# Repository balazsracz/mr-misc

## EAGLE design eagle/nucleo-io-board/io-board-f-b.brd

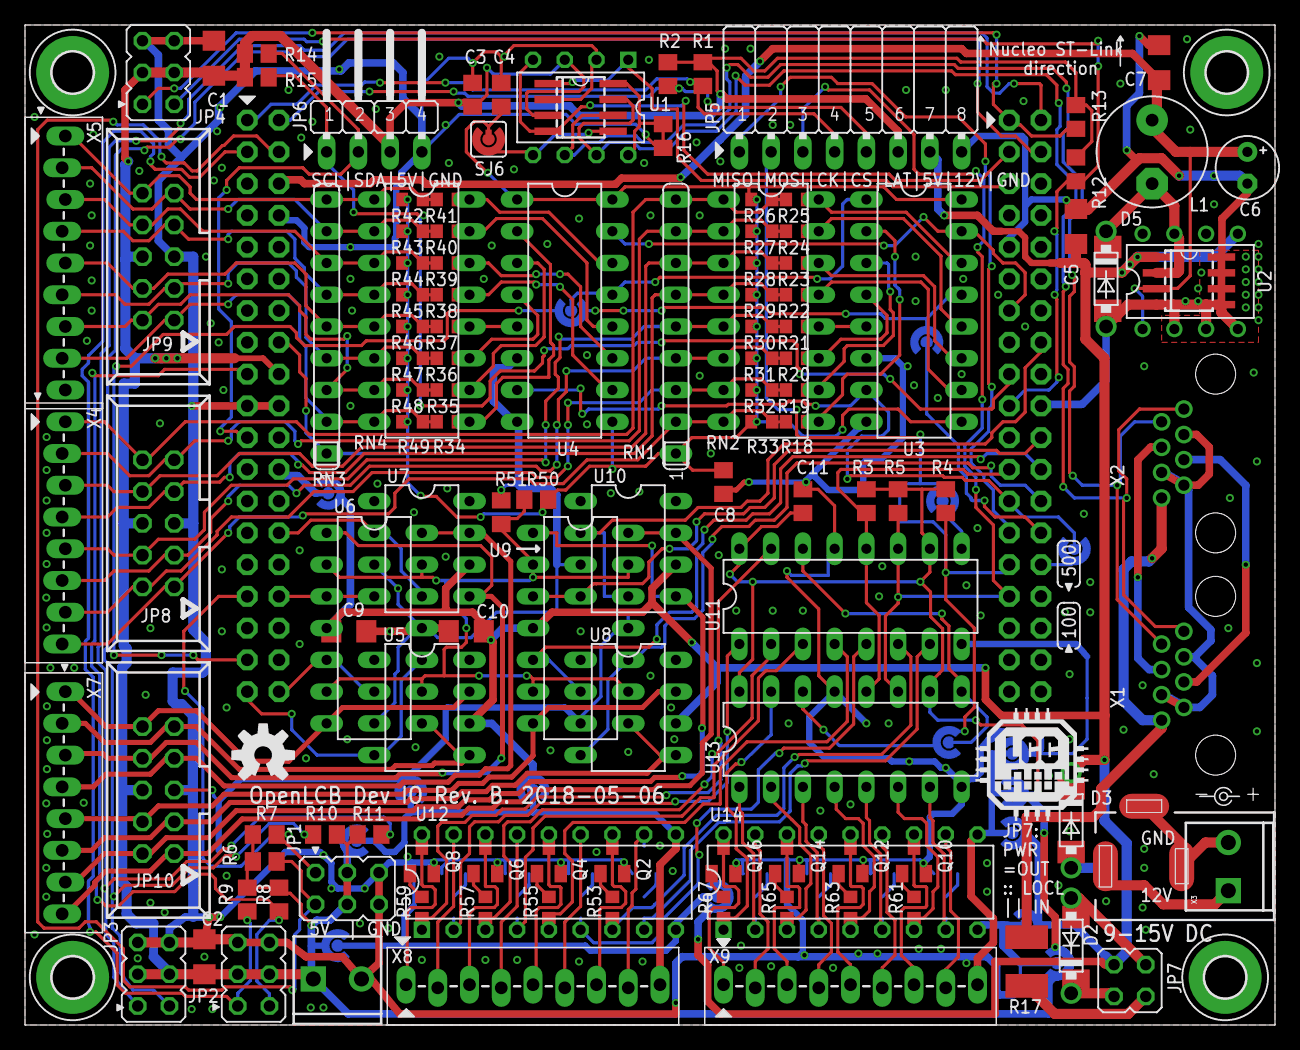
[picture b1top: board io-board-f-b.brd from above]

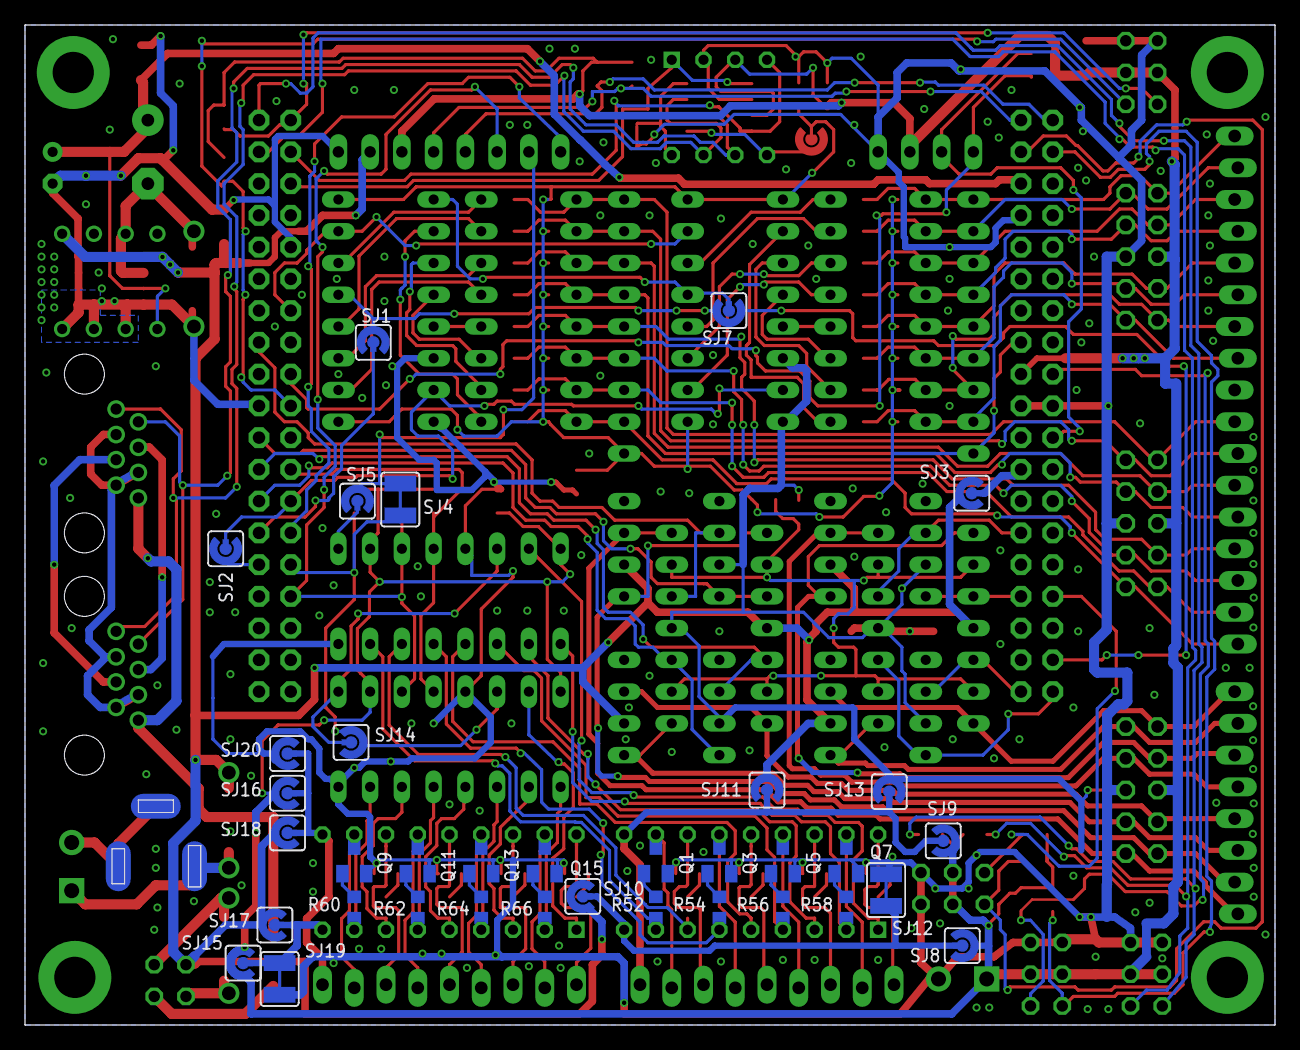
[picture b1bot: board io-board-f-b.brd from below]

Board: 2 copper layers, 100.0 x 80.0 mm, 169 parts (35 on the bottom side), 146 nets.

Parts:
C1, C2, C5, C7, C9, C10: C1206
C3, C4, C8, C11: C0805
C6: E2,5-5
D1, D3, D6: DIODEDO-214AA-NODOC; DO214AA-NODOC
D2, D4, D5: DO41-7.6
G1: NUCLEO_64_GENERIC; NUCLEO_BRD_BASE64
H1, H2, H3, H4: 3,3-PAD
J1: DCJ0202
JP1, JP2, JP3, JP4: JP3Q
JP5: JP8-FLATFEMALE; JP8F-FEM
JP6: JP4F
JP7: JP2Q
JP8: PORTB; CON10M
JP9: PORTA; CON10M
JP10: PORTC; CON10M
L1: L-US; L5-8,5
LG1: LCC_LOGO
LOGO1: DOC-OSHW-LOGOM; OSHW-LOGO-M
P1: 9-15V DC; POWER_USAGE
Q1, Q2, Q3, Q4, Q5, Q6, Q7, Q8, Q9, Q10, Q11, Q12, Q13, Q14, Q15, Q16: SOT23
R1, R2, R3, R4, R5, R6, R7, R8, R9, R10, R11, R12, R13, R16: R0805
R14, R15: 5k; R0805
R17: 500mA; PTC1812
R18, R19, R20, R21, R22, R23, R24, R25, R26, R27, R28, R29, R30, R31, R32, R33, R34, R35, R36, R37, R38, R39, R40, R41, R42, R43, R44, R45, R46, R47, R48, R49, R52, R53, R54, R55, R56, R57, R58, R59, R60, R61, R62, R63, R64, R65, R66, R67: R0603
R50, R51: 10k; R0805
RN1, RN3: 10K; SIL9
RN2, RN4: DIL16
SJ1, SJ2, SJ3, SJ5, SJ6, SJ7, SJ8, SJ9, SJ10, SJ11, SJ13, SJ14, SJ15, SJ16, SJ17, SJ18, SJ20: SJ_RND2
SJ4, SJ12, SJ19: SJW-C
U1: CAN-TXR-PDIP; DIL08
U1B: CAN-TXR-SO8; SO-08
U2: AP1509-50; SO-08
U2B: LM2574N-5.0; DIL08
U3, U4: 74HC166; DIL16
U5, U7, U8, U10: TC4427; DIL08-LONG
U6, U9: LM324N; DIL14
U11, U13: 74AHCT595N; DIL16
U12, U14: DIL18-THIN
X1, X2: RJ45-JACK; RJ45-PULSE-E5J88
X3, X6: SCREWTERMINAL-3.5MM-2_LOCK
X4, X7: M08-SCREW; 1X08_TERMINAL
X5: M09-SCREW; 1X09_TERMINAL
X8: PORTD; 1X09_TERMINAL
X9: PORTE; 1X09_TERMINAL

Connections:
+3V3: C4.1, C8.1, G1.3V3, R26.1, R27.1, R28.1, R29.1, R30.1, R31.1, R32.1, R33.1, R42.1, R43.1, R44.1, R45.1, R46.1, R47.1, R48.1, R49.1, R50.2, RN1.1, RN3.1, SJ6.P$1, U3.9, U3.16, U4.1, U4.9, U4.16
+5V: C1.1, C2.1, C3.1, C11.1, G1.5V2, JP1.3, JP1.4, JP2.3, JP2.4, JP3.3, JP3.4, JP4.3, JP4.4, JP5.6, JP6.3, JP8.6, JP9.6, JP10.6, R1.1, R2.1, R3.2, R4.2, R5.2, R6.1, R7.1, R8.1, R9.1, R10.1, R11.1, R12.1, R13.1, R14.1, R15.1, SJ8.P$2, SJ9.P$2, SJ15.P$2, SJ16.P$2, U1.3, U1B.3, U11.10, U11.16, U13.10, U13.16, X6.1
+12V: C5.1, C9.1, C10.1, D3.C, D4.C, JP5.7, JP7.2, SJ3.P$2, SJ10.P$2, SJ11.P$2, SJ17.P$2, SJ18.P$2, U2.1, U2B.5, U5.6, U6.4, U7.6, U8.6, U9.4, U10.6
ALT1: X1.4, X2.4
ALT2: X1.5, X2.5
CANH: U1.7, U1B.7, X1.1, X2.1
CANL: U1.6, U1B.6, X1.2, X2.2
CANRX: G1.PB8, U1.4, U1B.4
CANTX: G1.PB9, U1.1, U1B.1
CAN_RS: R16.1, U1.8, U1B.8
CAN_VIO: SJ6.P$2, U1.5, U1B.5
CMPREF: R50.1, R51.2, U6.2, U6.6, U6.9, U6.13, U9.2, U9.6, U9.9, U9.13
E_CS: G1.PC10, JP5.4, R1.2
E_LAT: G1.PC11, JP5.5, R2.2
E_MOSI: JP5.2, SJ4.2, SJ5.P$2
GND: C1.2, C2.2, C3.2, C4.2, C5.2, C6.-, C7.2, C8.2, C9.2, C10.2, C11.2, D5.A, D6.A, G1.GND3, G1.GND5, G1.GND6, G1.GND7, G1.GND8, J1.2, J1.2B, J1.3, J1.3B, JP1.5, JP1.6, JP2.5, JP2.6, JP3.5, JP3.6, JP4.5, JP4.6, JP5.8, JP6.4, JP8.5, JP9.5, JP10.5, Q1.2, Q2.2, Q3.2, Q4.2, Q5.2, Q6.2, Q7.2, Q8.2, Q9.2, Q10.2, Q11.2, Q12.2, Q13.2, Q14.2, Q15.2, Q16.2, R16.2, R51.1, SJ12.2, SJ13.P$2, SJ19.2, SJ20.P$2, U1.2, U1B.2, U2.4, U2.5, U2.6, U2.7, U2.8, U2B.2, U2B.3, U2B.4, U3.6, U3.8, U4.6, U4.8, U5.3, U6.11, U7.3, U8.3, U9.11, U10.3, U11.8, U11.13, U13.8, U13.13, X1.3, X1.6, X1.7, X2.3, X2.6, X2.7, X3.2, X5.9, X6.2
I2CSCL: G1.PB6, JP6.1, R15.2
I2CSDA: G1.PB7, JP6.2, R14.2
ILAT: G1.PA6, U3.15, U4.15
LPOWA: SJ8.P$1, SJ10.P$1, SJ12.1, U12.9
LPOWB: SJ9.P$1, SJ11.P$1, SJ13.P$1, U12.10, X8.9
MISO: G1.PB4, JP5.1
MISO2: G1.PC2, SJ1.P$2, SJ7.P$2, U3.13
MISO2_ALT: G1.PB14, SJ1.P$1
MOSI: G1.PB5, R4.1, SJ4.1, SJ14.P$2, U13.14
unnamed: R67.1, U13.15, U14.1
unnamed: Q16.3, U14.18, X9.1
unnamed: R66.1, U13.1, U14.2
unnamed: D3.A, D4.A, J1.1, J1.1B, X3.1
unnamed: JP8.10, R25.2, R26.2, RN1.9, RN2.1, X4.1
unnamed: JP9.1, R34.2, R49.2, RN3.2, RN4.8, X5.8
unnamed: Q15.3, U14.17, X9.2
unnamed: R65.1, U13.2, U14.3
unnamed: Q14.3, U14.16, X9.3
unnamed: R64.1, U13.3, U14.4
unnamed: Q13.3, U14.15, X9.4
unnamed: R63.1, U13.4, U14.5
unnamed: Q12.3, U14.14, X9.5
unnamed: JP9.2, R35.2, R48.2, RN3.3, RN4.7, X5.7
unnamed: JP9.3, R36.2, R47.2, RN3.4, RN4.6, X5.6
unnamed: Q13.1, R64.2
unnamed: R62.1, U13.5, U14.6
unnamed: Q11.3, U14.13, X9.6
unnamed: JP9.7, R38.2, R45.2, RN3.6, RN4.4, X5.4
unnamed: JP9.8, R39.2, R44.2, RN3.7, RN4.3, X5.3
unnamed: JP8.3, R20.2, R31.2, RN1.4, RN2.6, X4.6
unnamed: JP9.10, R41.2, R42.2, RN3.9, RN4.1, X5.1
unnamed: R34.1, RN4.9, U4.2
unnamed: R35.1, RN4.10, U4.3
unnamed: JP8.1, R18.2, R33.2, RN1.2, RN2.8, X4.8
unnamed: JP8.2, R19.2, R32.2, RN1.3, RN2.7, X4.7
unnamed: Q12.1, R63.2
unnamed: JP8.4, R21.2, R30.2, RN1.5, RN2.5, X4.5
unnamed: R36.1, RN4.11, U4.4
unnamed: R37.1, RN4.12, U4.5
unnamed: R38.1, RN4.13, U4.10
unnamed: R39.1, RN4.14, U4.11
unnamed: JP8.7, R22.2, R29.2, RN1.6, RN2.4, X4.4
unnamed: JP8.8, R23.2, R28.2, RN1.7, RN2.3, X4.3
unnamed: JP8.9, R24.2, R27.2, RN1.8, RN2.2, X4.2
unnamed: R40.1, RN4.15, U4.12
unnamed: R41.1, RN4.16, U4.14
unnamed: R61.1, U13.6, U14.7
unnamed: Q10.3, U14.12, X9.7
unnamed: R60.1, U13.7, U14.8
unnamed: Q9.3, U14.11, X9.8
unnamed: Q11.1, R62.2
unnamed: R18.1, RN2.9, U3.2
unnamed: D1.C, D2.C, JP7.1
unnamed: D1.A, D2.A, JP7.4
unnamed: R19.1, RN2.10, U3.3
unnamed: R20.1, RN2.11, U3.4
unnamed: R21.1, RN2.12, U3.5
unnamed: R22.1, RN2.13, U3.10
unnamed: R23.1, RN2.14, U3.11
unnamed: R24.1, RN2.15, U3.12
unnamed: R25.1, RN2.16, U3.14
unnamed: R59.1, U11.15, U12.1
unnamed: JP7.3, R17.1
unnamed: G1.VIN2, SJ3.P$1
unnamed: Q10.1, R61.2
unnamed: Q1.3, U12.11, X8.8
unnamed: Q16.1, R67.2
unnamed: Q15.1, R66.2
unnamed: JP9.4, R37.2, R46.2, RN3.5, RN4.5, X5.5
unnamed: JP9.9, R40.2, R43.2, RN3.8, RN4.2, X5.2
unnamed: Q9.1, R60.2
unnamed: Q8.3, U12.18, X8.1
unnamed: Q14.1, R65.2
unnamed: R58.1, U11.1, U12.2
unnamed: Q7.3, U12.17, X8.2
unnamed: R57.1, U11.2, U12.3
unnamed: Q6.3, U12.16, X8.3
unnamed: R56.1, U11.3, U12.4
unnamed: Q5.3, U12.15, X8.4
unnamed: R55.1, U11.4, U12.5
unnamed: Q4.3, U12.14, X8.5
unnamed: R54.1, U11.5, U12.6
unnamed: Q3.3, U12.13, X8.6
unnamed: R53.1, U11.6, U12.7
unnamed: Q2.3, U12.12, X8.7
unnamed: R52.1, U11.7, U12.8
unnamed: Q8.1, R59.2
unnamed: Q7.1, R58.2
unnamed: Q6.1, R57.2
unnamed: Q5.1, R56.2
unnamed: Q4.1, R55.2
unnamed: Q3.1, R54.2
unnamed: Q2.1, R53.2
unnamed: Q1.1, R52.2
OLAT: G1.PA8, R3.1, U11.12, U13.12
PWR_POS: R17.2, X1.8, X2.8
RPOWA: SJ15.P$1, SJ17.P$1, SJ19.1, U14.9
RPOWB: SJ16.P$1, SJ18.P$1, SJ20.P$1, U14.10, X9.9
SCK: G1.PB3, JP5.3, R5.1, U11.11, U13.11
SCK2: G1.PB10, SJ2.P$1, U3.7, U4.7
SCK2_ALT: G1.PB13, SJ2.P$2
SLNK1: SJ14.P$1, U11.14, U13.9
SLNK2: SJ5.P$1, U11.9
SLNK3: SJ7.P$1, U3.1, U4.13
SRV1: G1.PC9, JP4.2, R13.2
SRV2: G1.PC7, JP4.1, R12.2
SRV3: G1.PC8, JP3.2, R11.2
SRV4: G1.PC6, JP3.1, R10.2
SRV5: G1.PC12, JP2.2, R9.2
SRV6: G1.PA15, JP2.1, R8.2
SRV7: G1.PF1-PH1, JP1.2, R7.2
SRV8: G1.PD2, JP1.1, R6.2
SW: D5.C, D6.C, L1.2, U2.2, U2B.7
TDRV1: G1.PB12, U9.12, U10.2
TDRV2: G1.PB2, U9.3, U10.4
TDRV3: G1.PB15, U8.4, U9.10
TDRV4: G1.PB1, U8.2, U9.5
TDRV5: G1.PA0, U6.12, U7.2
TDRV6: G1.PA4, U6.3, U7.4
TDRV7: G1.PC3, U5.4, U6.10
TDRV8: G1.PC0, U5.2, U6.5
TOUT1: JP10.10, U5.7, U6.7, X7.1
TOUT2: JP10.9, U5.5, U6.8, X7.2
TOUT3: JP10.8, U6.1, U7.5, X7.3
TOUT4: JP10.7, U6.14, U7.7, X7.4
TOUT5: JP10.4, U8.7, U9.7, X7.5
TOUT6: JP10.3, U8.5, U9.8, X7.6
TOUT7: JP10.2, U9.1, U10.5, X7.7
TOUT8: JP10.1, U9.14, U10.7, X7.8
V+: C6.+, C7.1, G1.E5V, L1.1, U2.3, U2B.1
